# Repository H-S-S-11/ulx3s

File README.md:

Fork of ULX3S for PCB layout practice

# ULX3S PCB

[ULX3S](http://radiona.org/ulx3s) = [University digital Logic](https://www.fer.unizg.hr/en/course/diglog) Learning
Xtensible board release 3 with SDRAM,
Successor of [ULX2S](http://github.com/emard/ulx2s).

[Manual](/doc/MANUAL.md) *
[Quickstart Binaries](http://github.com/emard/ulx3s-bin) *
[ULX3S at Kitspace](https://kitspace.org/boards/github.com/emard/ulx3s)

3D preview

Prototypes available
at [SKRIPTARNICA](http://skriptarnica.hr/vijest.aspx?newsID=1466),
local shop inside of [FER](https://www.fer.unizg.hr/) university.

This is a small (94x51 mm) standalone FPGA board 
for education, research and general purpose, with a full 
featured selection of chips which I all wanted on
a low-cost PCB, but haven't found on the market.
It's open source and open hardware because if it is
good for our development of [f32c](http://github.com/f32c/f32c) SOC,
it should be also good to other projects.

ULX3S will carry all digital logic on our
research, [education](https://www.fer.unizg.hr/en/course/diglog) and
[makerspace](https://radiona.org) projects in next 5 years.

ULX3S is standalone embeddable gadget with onboard display, buttons,
storage, WiFi and compatible connectors.

ULX3S can do things no other board can.

ULX3S can self-reflash with a bitstream sent
remotely from web interface over WiFi or from SD
card browsed by onboard OLED display and buttons.

ULX3S can completely power down and wakeup from
battery backed RTC.

ULX3S has rich range of chips and connectivity
required for many other open source projects:
SDRAM, USB, PS/2, SDCARD, Digital Video, FLASH, RTC, I2C, OLED, AUDIO, ADC,
onboard FM/ASK antenna 88-433.92 MHz and 56 GPIO pins routed as differential
pairs and have pinout that is PMOD compatible. There are 12 true
differential bidirectional pairs and 16 single-ended pairs.

ULX3S is sufficiently equipped to
emulate [Amiga](https://github.com/emard/Minimig_ECS) retro
computer and run its games, but can do much more like
running [Linux](https://twitter.com/fpga_dave/status/1053290842809683968).

[Schematics](/doc/schematics.pdf) and PCB started with KiCAD 4.
After version v1.8 project switched to KiCAD 5 PCB editor:

    kicad ulx3s.pro

View generated gerbers

    gerbv -p plot/ulx3s.gvp

# Features

FPGA: Lattice ECP5 [LFE5U-85F-6BG381C](http://www.latticesemi.com/~/media/LatticeSemi/Documents/DataSheets/ECP5/FPGA-DS-02012.pdf?document_id=50461) (12/25/45/85K LUT)

USB: FTDI [FT231XS](https://www.ftdichip.com/Support/Documents/DataSheets/ICs/DS_FT231X.pdf) (500kbit JTAG and 3Mbit USB-serial)

GPIO: 56 pins (12 true differential pairs, 16 single-ended pairs),
[PMOD](https://reference.digilentinc.com/_media/pmod:pmod:originalPmodInterfaceSpecification.pdf) compatible
with power out 3.3V/1A 2.5V/1.5A

RAM: 16-bit SDRAM [MT48LC32M16](https://www.micron.com/~/media/Documents/Products/Data%20Sheet/DRAM/256Mb_sdr.pdf) (8/16/32/64 MB)

Flash: Quad-SPI Flash [IS25LP128F](http://www.issi.com/WW/pdf/25LP-WP128F.pdf) (4/8/16 MB for FPGA config and user data)

Storage: Micro-SD slot

LEDs: 11 (8 blink-LEDs, 2 USB LEDs, 1 WiFi LED)

Buttons: 7 (4 direction, 2 fire, 1 power button)

Audio: 3.5 mm jack with 4 contacts (analog stereo + digital audio or composite video)

Video: GPDI connector with 3.3V-5V I2C bidirectional level shifter

Display: placeholder for 0.96" SPI COLOR OLED [SSD1331](https://drive.google.com/file/d/0B5lkVYnewKTGRlpxcEdWaXNvWnM/view)

WiFi+bluetooth: placeholder for [ESP-32](https://www.espressif.com/sites/default/files/documentation/esp32_datasheet_en.pdf) (Standalone JTAG web interface over WiFi)

Antenna: 88-108/433 MHz FM/ASK onboard

ADC: 8 channels, 12 bit, 1 MSa/s [MAX11125](https://datasheets.maximintegrated.com/en/ds/MAX11120-MAX11128.pdf) (4/8-ch, 8/10/12-bit, 0.5/1 MSa/s)

Power: 3 Switching voltage regulators: 1.1V, 2.5V, 3.3V (1.5/2A)

Clock: 25 MHz onboard, external differential clock input

Low power sleep: 5uA/5V standby, RTC [MCP7940N](http://ww1.microchip.com/downloads/en/DeviceDoc/20005010F.pdf) clock wakeup, power button, 32768 Hz quartz and battery

GPDI is General Purpose Differential Interface,
Electrically LVDS, mostly TMDS tolerant
female receptacle more-or-less compatible
with digital monitors/TVs

# Production

Independent production
like [q3k](https://twitter.com/q3k/status/1029010026269167618) or
[samlittlewood](https://twitter.com/samlittlewood/status/1108531208001077250) is
welcome and desirable under conditions of [modified MIT LICENSE](/LICENSE.md).
If you do manual assembly here is [minimal parts list](/doc/MINIMAL.md).

ZIP the gerbers and send them to manufacturer:

    zip -r /tmp/ulx3s.zip plot/ulx3s

If you are going to order this project by yourself, it is important
what manufacturer to choose for PCBA (PCB and Assembly) service.

Parts can be ordered from [Detailed BOM](/doc/ulx3s_bom.csv)
or from [ULX3S at Kitspace](https://kitspace.org/boards/github.com/emard/ulx3s),
which automatically submits [Simplified 1-click BOM](/1-click-bom.tsv) by
clicking on "Digikey" or "Mouser" button. On each click, Digikey and Mouser will keep
accumulating the BOM in the shopping cart. Number of unique parts on Digikey and Mouser
should be equal but DigiKey may split some parts (LEDs) in multiple rows.
To reset shopping cart, click "New Cart" or "New Basket".
Kitspace may be updated with about 1 day delay after this project update.

Choose PCBA manufacturer which can produce PCB of IPC CLASS 3 quality,
5/5 mil trace resolution and 0.2 mm holes.
Avoid manufacturer who claims "quality" and "satisfaction" but doesn't
really know what will be IPC CLASS rating for this project.

PCBA manufacturer prices for the parts should be approximately equal as those
from distributors like [Mouser](http://www.mouser.com) or [DigiKey](http://www.digikey.com).
Avoid any PCBA manufacturer who asks 3$ for the 1$ part or 40$ for the 30$ part.
Select [Mouser](http://www.mouser.com) language/location icon to PCBA manufacturer
country of origin and $-currency to check is PCBA manufacturer telling the truth
about prices.

Before soldering the parts, ask manufacturer for [pictures](/pic/ulx3sb-v18.jpg) of PCB.
CLASS 3 demands, among other things, that all drill holes stay inside of VIA pads.
If some holes [break-out](/pic/ulx3sb-v18-breakout-c19.png) from pads,
ask manufacturer to make new PCBs with better drill and copper layer alignment.

[PCBCART](http://www.pcbcart.com) offers CLASS 3 quality and assembly at reasonable cost.
Prices for the parts are equal to [Mouser](http://www.mouser.com).

Don't pay everything at once. Following payment phases during the
PCBA production are recommended:

    1. Pay for the parts
    2. Manufacturer orders the parts and optionally negotiates with you about part numbers.
       Depending on market availability, some parts may come in different physical package.
    3. Send updated gerbers which fit to ordered parts.
    4. Pay for PCB
    5. Manufacturer sends pictures of produced PCB for your inspection.
       If anything looks suspicious, ask also for X-ray imaging.
    6. Pay for the assembly and shipping.

Nobody wants quality issues, so it is good to ask if manufacturer has qualified personnel
able to follow instructions 
for [ULX3S self-test](https://github.com/emard/ulx3s-bin) before shipping.

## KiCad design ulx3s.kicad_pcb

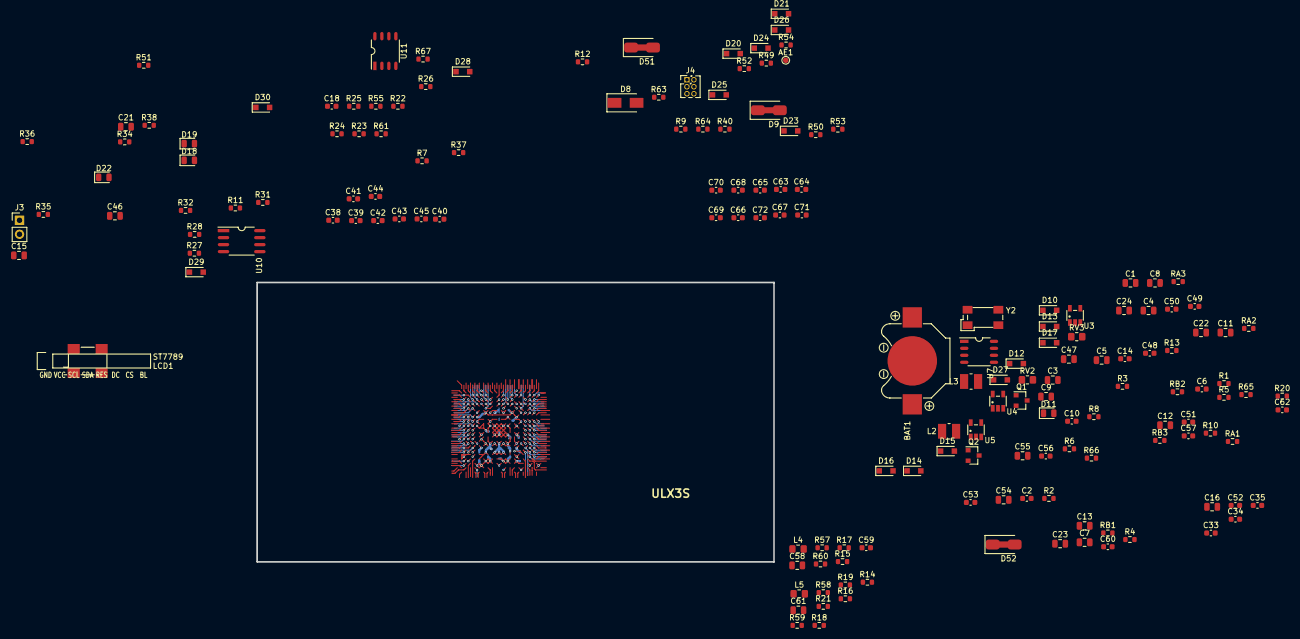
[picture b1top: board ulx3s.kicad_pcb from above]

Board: 4 copper layers, 164 parts (1 on the bottom side), 62 nets.

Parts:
AE1: 433MHz; TestPoint_Pad_D1.0mm
BAT1: CR1225; Keystone_3000_1x12mm-CoinCell
C1, C3, C4, C5, C7, C8, C9, C11, C12, C15, C21, C54, C55, C58, C61: 22uF; C_0805_2012Metric
C2, C6, C10, C18: 100pF; C_0603_1608Metric
C13, C16, C22, C23, C24, C46, C47: 2.2uF; C_0805_2012Metric
C14, C59, C60, C62: 220nF; C_0603_1608Metric
C33, C34, C35, C38, C39, C40, C41, C42, C43, C44, C45, C48, C49, C50, C51, C52, C53, C63, C64, C65, C66, C67, C68, C69, C70, C71, C72: 22nF; C_0603_1608Metric
C56, C57: 4.7pF; C_0603_1608Metric
D8: STPS2L40AF; D_SMA
D9, D51, D52: 0; D_SMA_Jumper_NC
D10, D13, D14, D16, D17, D23, D24, D25, D26, D27, D28, D29: 1N914; D_SOD-323_HandSoldering
D11, D19: RED; LED_0805_2012Metric
D12, D15: BAT54W; D_SOD-323_HandSoldering
D18: GREEN; LED_0805_2012Metric
D20, D21, D30: 3.6V; D_SOD-323_HandSoldering
D22: BLUE; LED_0805_2012Metric
J3: WIFI_OFF; PinHeader_1x02_P2.54mm_Vertical
J4: CONN_02X03; PinHeader_2x03_P1.27mm_Vertical
L1, L2, L3: 2.2uH; L_1008_1210
L4, L5: 33uH; L_0805_2012Metric_Pad1.15x1.40mm_HandSolder
LCD1: ST7789; st7789
Q1: BC857; SOT-23
Q2: 2N7002; SOT-23
R1, R3, R4, R25, R26: 4.7k; R_0603_1608Metric
R2: 18k; R_0603_1608Metric
R5: 2.2M; R_0603_1608Metric
R6, R8, R14, R18, R40, R54, R57, R66: 1.1k; R_0603_1608Metric
R7, R10, R17, R21, R51, R60: 130; R_0603_1608Metric
R9, R13, R31, R32, R34, R63, R64: 15k; R_0603_1608Metric
R11, R12, R27, R28, R55: 10k; R_0603_1608Metric
R15, R19, R35, R36, R37, R58, R61, R65, R67: 549; R_0603_1608Metric
R16, R20, R59: 270; R_0603_1608Metric
R22, R23: 3.3k; R_0603_1608Metric
R24: 100k; R_0603_1608Metric
R38: 0.47; R_0603_1608Metric
R49, R50, R52, R53: 27; R_0603_1608Metric
RA1, RA2, RA3: 15k; R_0603_1608Metric
RB1: 18k; R_0603_1608Metric
RB2: 4.7k; R_0603_1608Metric
RB3: 3.3k; R_0603_1608Metric
RV2, RV3: 0; R_0805_2012Metric_Pad1.20x1.40mm_HandSolder
U3, U4, U5: TLV62569DBV; TSOT-25
U7: MCP7940NT; SOT96-1
U10: IS25LP128F-JBLE; SOA008-150-208mil
U11: PCA9306D; SM8
Y2: 32768Hz; Crystal_SMD_ABS25

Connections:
2V5_3V3: C47.1, C48.1, C49.1, C53.1, R51.1, RV2.2, RV3.1
+2V5: R22.1, R23.1, RV2.1, U11.2
+3V3: C16.1, C21.1, C33.1, C34.1, C35.1, C46.1, C50.1, C51.1, C52.1, D11.2, D14.1, J4.2, L4.1, L5.1, LCD1.1, LCD1.4, R7.1, R11.1, R12.1, R27.1, R28.1, R31.1, R32.1, R34.1, R38.2, R65.1, RV3.2, U10.8, U11.8
+5V: C1.1, C5.1, C9.1, C13.1, D8.1, D9.2, D51.1, D52.2, Q1.2, R3.1, R24.1, R25.1, R26.1, U3.4, U4.4, U5.4
/analog/ADC3V3: C58.1, C59.1, L4.2
/analog/ADCD3V3: C61.1, C62.1, L5.2
/analog/AUDIO_L: R14.2, R15.2, R16.2, R17.2
/analog/AUDIO_R: R18.2, R19.2, R20.2, R21.2
/analog/AUDIO_V: R57.2, R58.2, R59.2, R60.2
/blinkey/LED_PWREN: D18.1, R36.1
/blinkey/LED_TXLED: D19.1, R37.2
/flash/FLASH_MISO: R28.2, U10.2
/flash/FLASH_MOSI: R27.2, U10.5
/flash/FLASH_nHOLD: R12.2, U10.7
/flash/FLASH_nWP: R11.2, U10.3
/flash/FPGA_PROGRAMN: D28.2, D29.2, R31.2
/gpdi/VREF2: C18.1, R24.2, U11.7
/power/FB1: C2.2, RA1.2, RB1.2, U3.5
/power/FB2: C10.2, RA2.2, RB2.2, U4.5
/power/FB3: C6.2, RA3.2, RB3.2, U5.5
/power/FTDI_nSUSPEND: D12.2, R10.1
/power/HOLD: D11.1, R4.1
/power/L1: L1.1, U3.3
/power/L2: L2.1, U4.3
/power/L3: L3.1, U5.3
/power/OSCI_32k: C56.2, U7.1, Y2.4
/power/OSCO_32k: C57.2, U7.2, Y2.1
/power/P1V1: C2.1, C3.1, C4.1, C22.1, L1.2, RA1.1
/power/P2V5: C10.1, C11.1, C12.1, C23.1, L2.2, RA2.1
/power/P3V3: C6.1, C7.1, C8.1, C24.1, L3.2, RA3.1
/power/PWREN: D12.1, R1.2, R2.1, R4.2, R8.1, U3.1, U4.1, U5.1
/power/RTCVDD: C55.1, R65.2, U7.8
/power/SHD: Q2.3, R8.2
/power/SHUT: C14.1, D14.2, D15.1, Q2.1, R5.1
/power/VBAT: BAT1.1, C54.1, U7.3
/power/WAKE: D10.1, R1.1
/power/WAKEUPn: D16.2, D27.1, R6.2, U7.7
/power/WKUP: C13.2, D10.2, D13.1, Q1.3
/power/WKn: Q1.1, R6.1
/wifi/SD3V3: C15.1, R38.1
/wifi/WIFIEN: J3.2, R35.2
FPDI_HPD: D30.1, R67.1
FPDI_SCL: R23.2, U7.6, U11.3
FPDI_SDA: R22.2, U7.5, U11.4
FT2V5: D19.2, R9.2
FTDI_nSLEEP: D18.2, R10.2
GND: BAT1.2, C1.2, C3.2, C4.2, C5.2, C7.2, C8.2, C9.2, C11.2, C12.2, C14.2, C15.2, C16.2, C18.2, C21.2, C22.2, C23.2, C24.2, C33.2, C34.2, C35.2, C46.2, C47.2, C48.2, C49.2, C50.2, C51.2, C52.2, C53.2, C54.2, C55.2, C56.1, C57.1, C58.2, C59.2, C60.2, C61.2, C62.2, D13.2, D20.2, D21.2, D30.2, J3.1, J4.1, LCD1.2, Q2.2, R2.2, R5.2, R13.2, R36.2, RB1.1, RB2.1, RB3.1, U3.2, U4.2, U5.2, U7.4, U10.4, U11.1
GPDI_SCL: R25.2, U11.6
GPDI_SDA: R26.2, U11.5
JTAG_TMS: D22.1, J4.5
unnamed: D23.2, R63.1
unnamed: D24.1, R40.1
unnamed: D25.2, R64.1
unnamed: D26.1, R54.2
unnamed: D27.2, R66.2
PWRBTn: C60.1, D16.1, D17.1, D28.1, R3.2
SHUTDOWN: D15.2, R13.1
USB_FPGA_D+: D20.1, R40.2, R53.1, R63.2
USB_FPGA_D-: D21.1, R52.1, R54.1, R64.2
USB_FPGA_PULL_D+: D23.1, D24.2
USB_FPGA_PULL_D-: D25.1, D26.2
WIFI_EN: R34.2, R35.1

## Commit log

2021-01-31 reassign footprints
2021-02-01 fpga power
2021-02-01 finish breakout
2021-02-01 breakout most of remaining pads
2021-02-01 shuffle capacitors
2021-02-01 full breakout
2021-02-01 finishing touches to bga breakout
2021-02-01 replace most top layer fills with traces
2021-02-02 convert top layer pours to traces
